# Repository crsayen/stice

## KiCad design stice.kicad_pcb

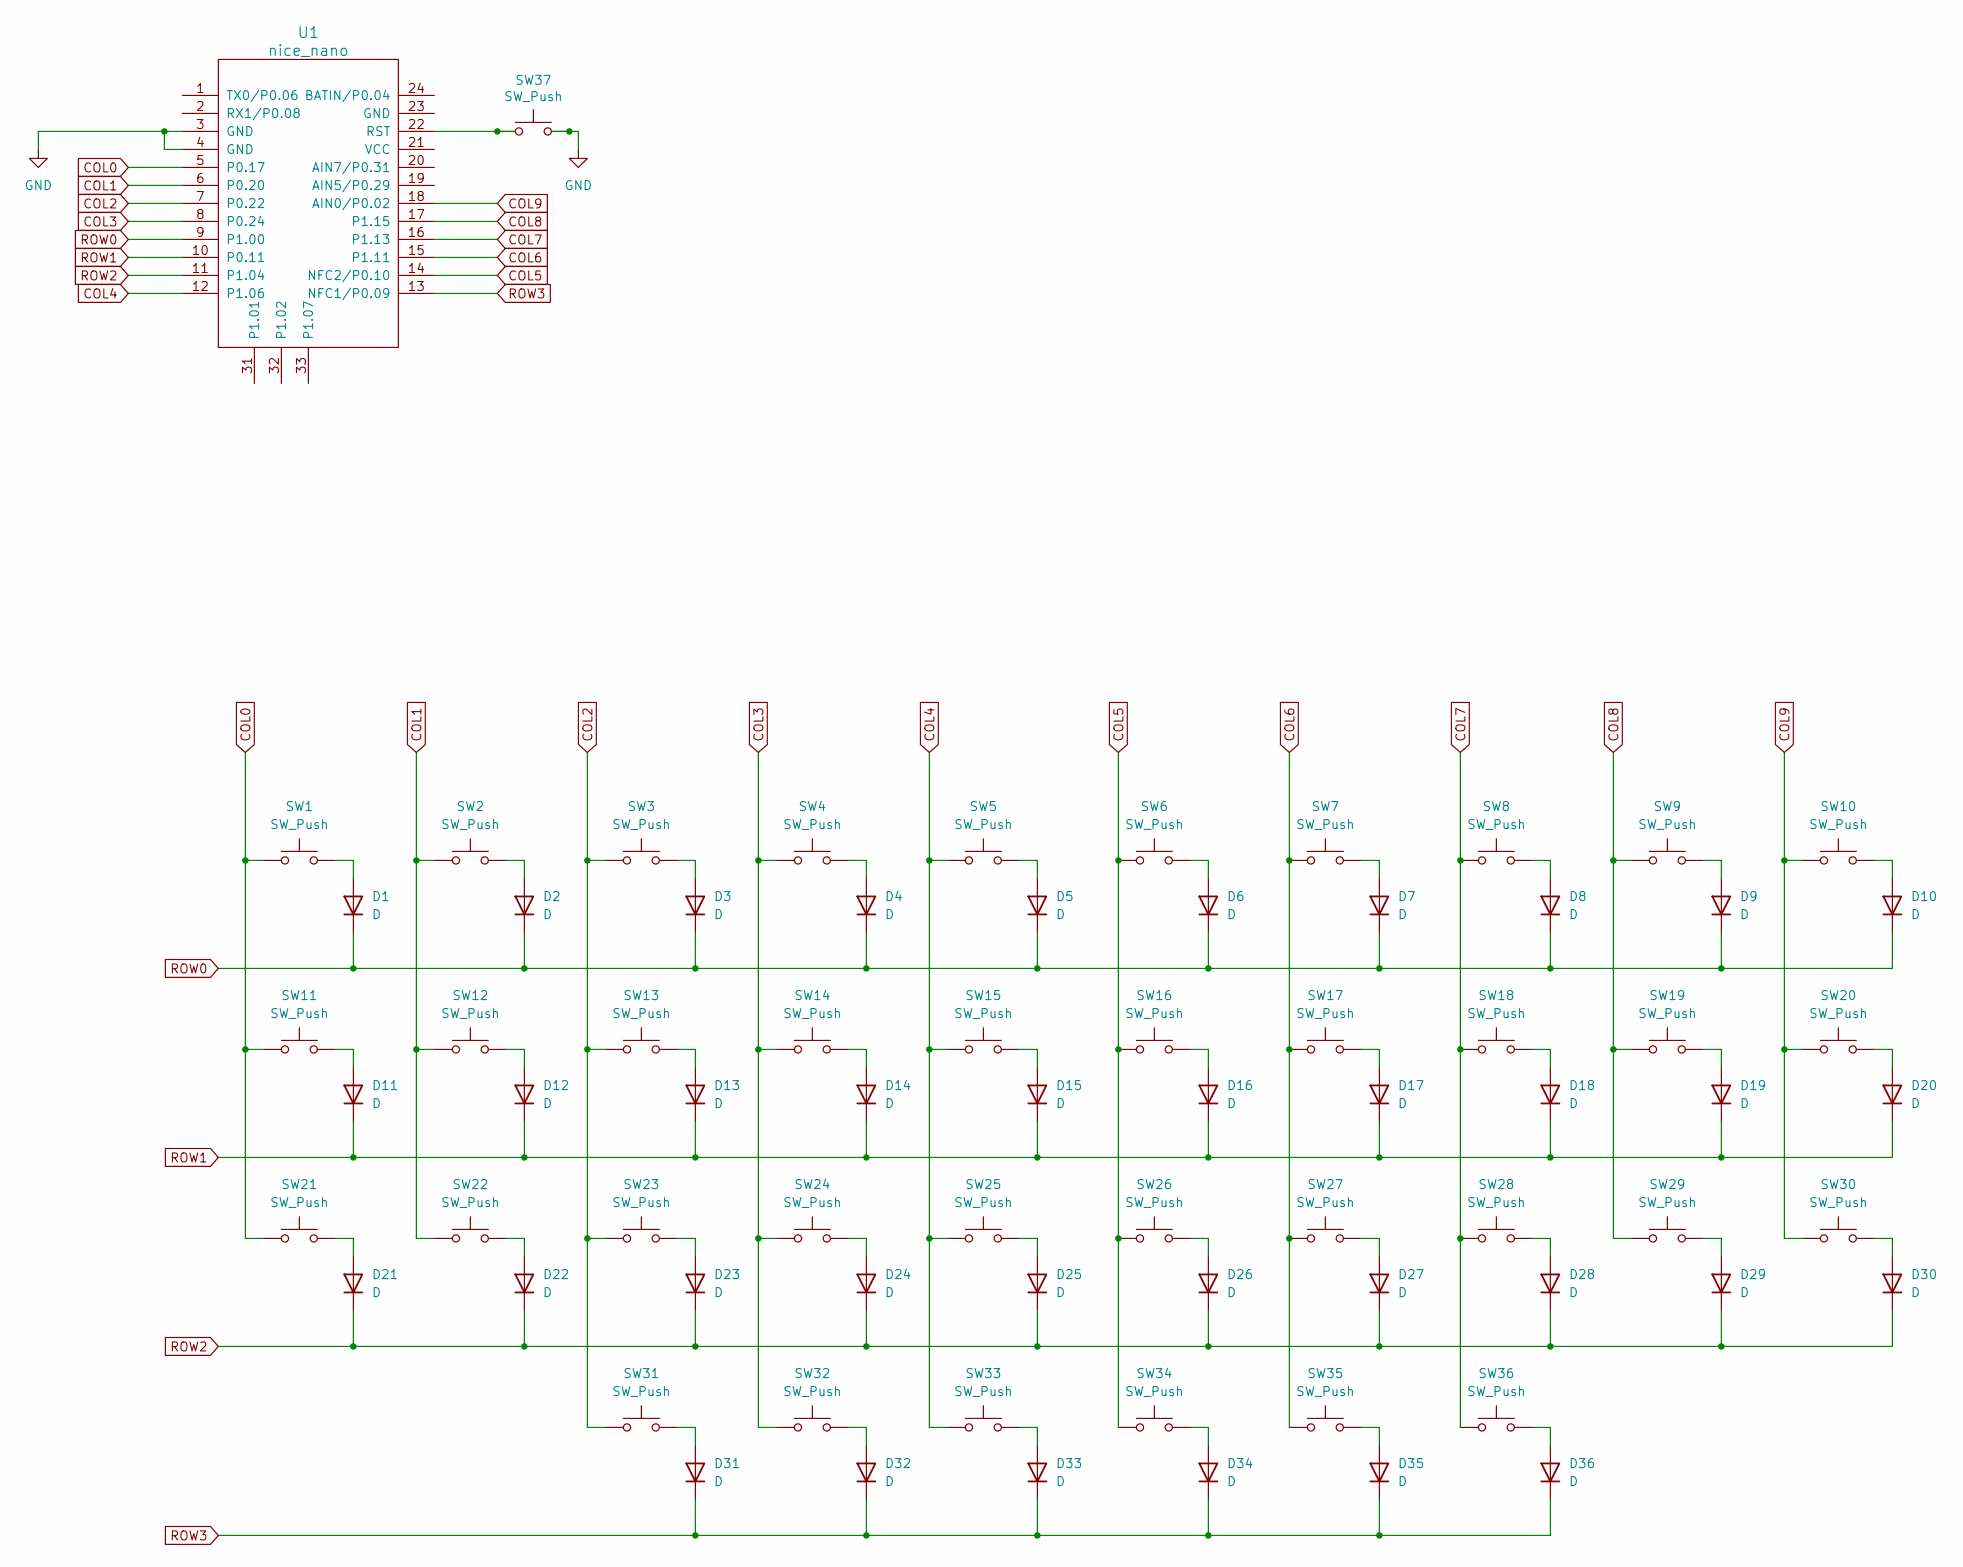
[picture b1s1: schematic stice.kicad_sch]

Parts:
D1, D2, D3, D4, D5, D6, D7, D8, D9, D10, D11, D12, D13, D14, D15, D16, D17, D18, D19, D20, D21, D22, D23, D24, D25, D26, D27, D28, D29, D30, D31, D32, D33, D34, D35, D36: D; D_SOD-123
SW1, SW2, SW3, SW4, SW5, SW6, SW7, SW8, SW9, SW10, SW11, SW12, SW13, SW14, SW15, SW16, SW17, SW18, SW19, SW20, SW21, SW22, SW23, SW24, SW25, SW26, SW27, SW28, SW29, SW30, SW31, SW32, SW33, SW34, SW35, SW36: SW_Push; SW_Hotswap_Kailh_MX_1.00u
SW37: SW_Push; SW_SPST_3x3
U1: nice_nano; Elite-C

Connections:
COL0: SW1.1, SW11.1, SW21.1, U1.5 (P0.17)
COL1: SW2.1, SW12.1, SW22.1, U1.6 (P0.20)
COL2: SW3.1, SW13.1, SW23.1, SW31.1, U1.7 (P0.22)
COL3: SW4.1, SW14.1, SW24.1, SW32.1, U1.8 (P0.24)
COL4: SW5.1, SW15.1, SW25.1, SW33.1, U1.12 (P1.06)
COL5: SW6.1, SW16.1, SW26.1, SW34.1, U1.14 (NFC2/P0.10)
COL6: SW7.1, SW17.1, SW27.1, SW35.1, U1.15 (P1.11)
COL7: SW8.1, SW18.1, SW28.1, SW36.1, U1.16 (P1.13)
COL8: SW9.1, SW19.1, SW29.1, U1.17 (P1.15)
COL9: SW10.1, SW20.1, SW30.1, U1.18 (AIN0/P0.02)
GND: SW37.2, U1.3 (GND), U1.4 (GND)
unnamed: D1.2 (A), SW1.2
unnamed: D2.2 (A), SW2.2
unnamed: D3.2 (A), SW3.2
unnamed: D4.2 (A), SW4.2
unnamed: D5.2 (A), SW5.2
unnamed: D6.2 (A), SW6.2
unnamed: D7.2 (A), SW7.2
unnamed: D8.2 (A), SW8.2
unnamed: D9.2 (A), SW9.2
unnamed: D10.2 (A), SW10.2
unnamed: D11.2 (A), SW11.2
unnamed: D12.2 (A), SW12.2
unnamed: D13.2 (A), SW13.2
unnamed: D14.2 (A), SW14.2
unnamed: D15.2 (A), SW15.2
unnamed: D16.2 (A), SW16.2
unnamed: D17.2 (A), SW17.2
unnamed: D18.2 (A), SW18.2
unnamed: D19.2 (A), SW19.2
unnamed: D20.2 (A), SW20.2
unnamed: D21.2 (A), SW21.2
unnamed: D22.2 (A), SW22.2
unnamed: D23.2 (A), SW23.2
unnamed: D24.2 (A), SW24.2
unnamed: D25.2 (A), SW25.2
unnamed: D26.2 (A), SW26.2
unnamed: D27.2 (A), SW27.2
unnamed: D28.2 (A), SW28.2
unnamed: D29.2 (A), SW29.2
unnamed: D30.2 (A), SW30.2
unnamed: D31.2 (A), SW31.2
unnamed: D32.2 (A), SW32.2
unnamed: D33.2 (A), SW33.2
unnamed: D34.2 (A), SW34.2
unnamed: D35.2 (A), SW35.2
unnamed: D36.2 (A), SW36.2
unnamed: SW37.1, U1.22 (RST)
ROW0: D1.1 (K), D2.1 (K), D3.1 (K), D4.1 (K), D5.1 (K), D6.1 (K), D7.1 (K), D8.1 (K), D9.1 (K), D10.1 (K), U1.9 (P1.00)
ROW1: D11.1 (K), D12.1 (K), D13.1 (K), D14.1 (K), D15.1 (K), D16.1 (K), D17.1 (K), D18.1 (K), D19.1 (K), D20.1 (K), U1.10 (P0.11)
ROW2: D21.1 (K), D22.1 (K), D23.1 (K), D24.1 (K), D25.1 (K), D26.1 (K), D27.1 (K), D28.1 (K), D29.1 (K), D30.1 (K), U1.11 (P1.04)
ROW3: D31.1 (K), D32.1 (K), D33.1 (K), D34.1 (K), D35.1 (K), D36.1 (K), U1.13 (NFC1/P0.09)

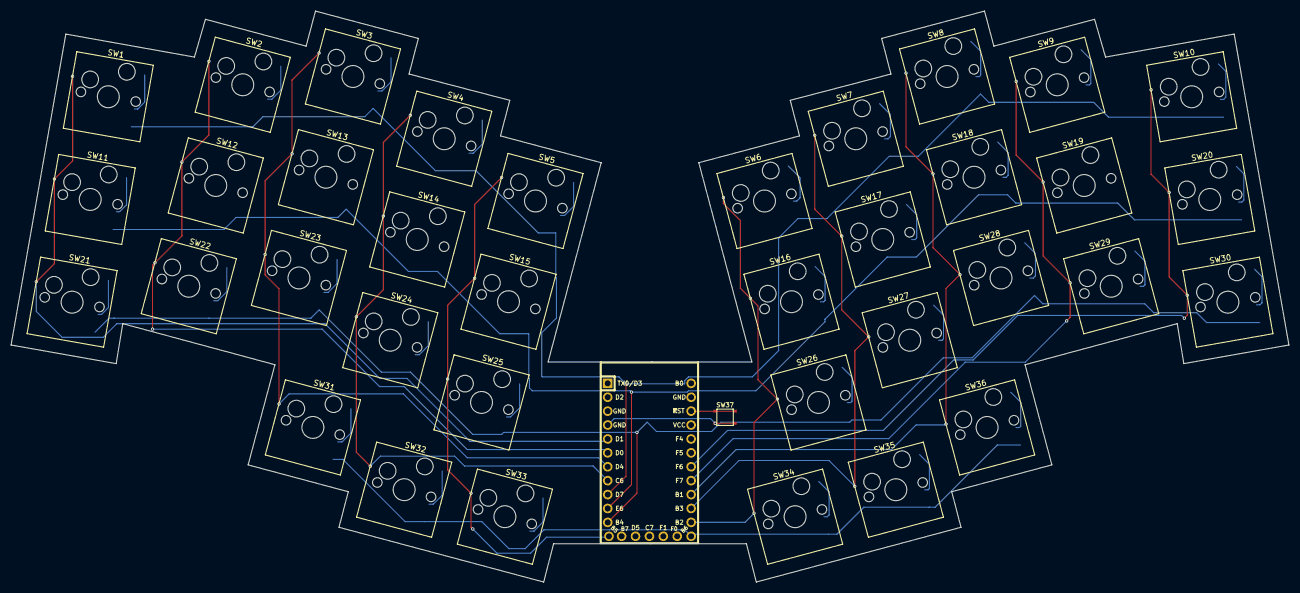
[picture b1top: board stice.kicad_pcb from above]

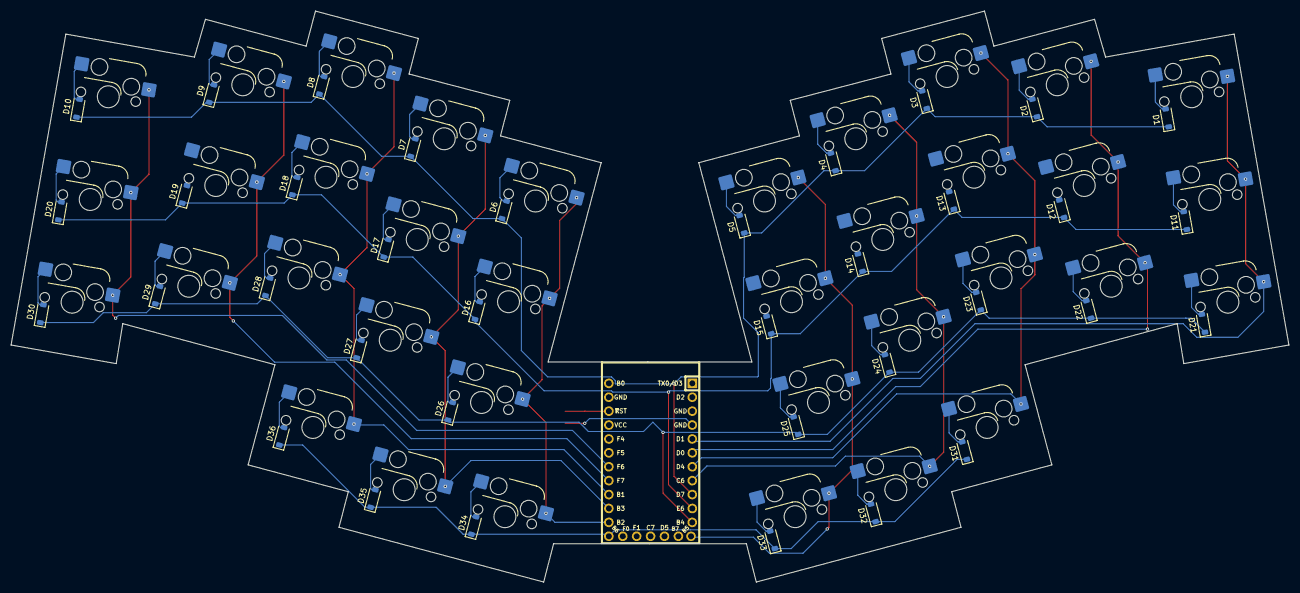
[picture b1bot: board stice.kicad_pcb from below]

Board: 2 copper layers, 233.4 x 104.3 mm, 74 parts (36 on the bottom side), 52 nets.

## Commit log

2024-11-02 init
2024-11-03 outline done
